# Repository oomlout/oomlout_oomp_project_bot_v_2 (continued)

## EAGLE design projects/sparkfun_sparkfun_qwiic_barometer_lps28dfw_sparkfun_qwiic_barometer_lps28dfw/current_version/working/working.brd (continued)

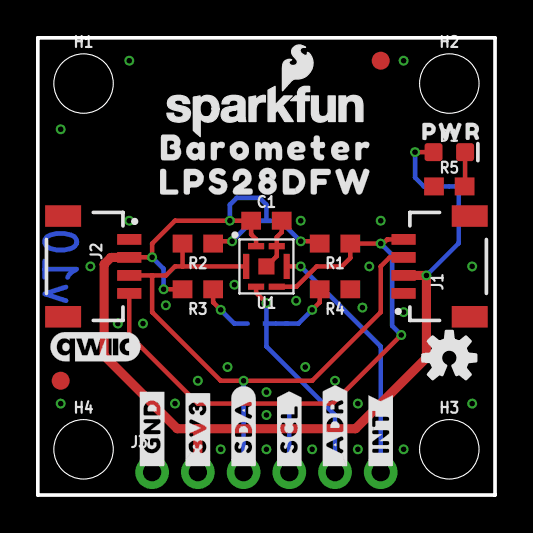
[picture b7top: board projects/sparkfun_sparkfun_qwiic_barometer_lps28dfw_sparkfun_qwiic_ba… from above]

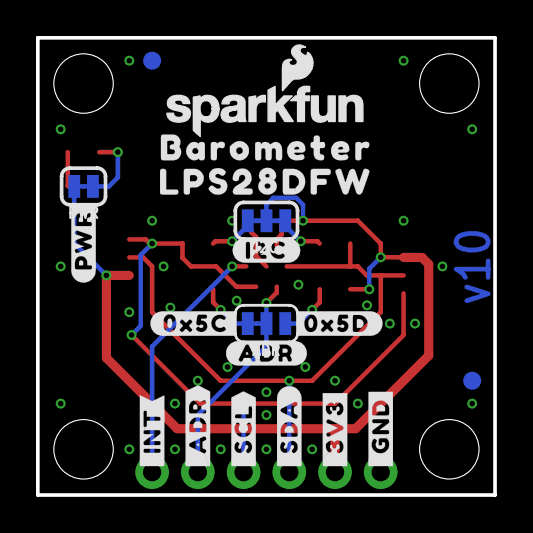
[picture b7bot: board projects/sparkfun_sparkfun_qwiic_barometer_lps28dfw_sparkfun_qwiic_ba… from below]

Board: 2 copper layers, 25.4 x 25.4 mm, 50 parts (19 on the bottom side), 12 nets.

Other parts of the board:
LOGO4: SFE_LOGO_NAME_FLAME.1_INCH; SFE_LOGO_NAME_FLAME_.1
U$1, U$2: #_GND#0
U$3, U$4: #_3V3#0
U$5, U$6: #_SDA#0
U$7, U$8: #_SCL#0
U$9: #I2C#0
U$10: #ADR#0
U$11, U$14: BAROMETER0
U$12, U$15: LPS28DFW0
U$13: #PWR#0
U$16: #0X5D#0
U$17: #0X5C#0
U$18: PWR0
U$19: ORDERING_INSTRUCTIONS
U$20, U$21: #_INT#0
U$22, U$23: #_ADR#0
